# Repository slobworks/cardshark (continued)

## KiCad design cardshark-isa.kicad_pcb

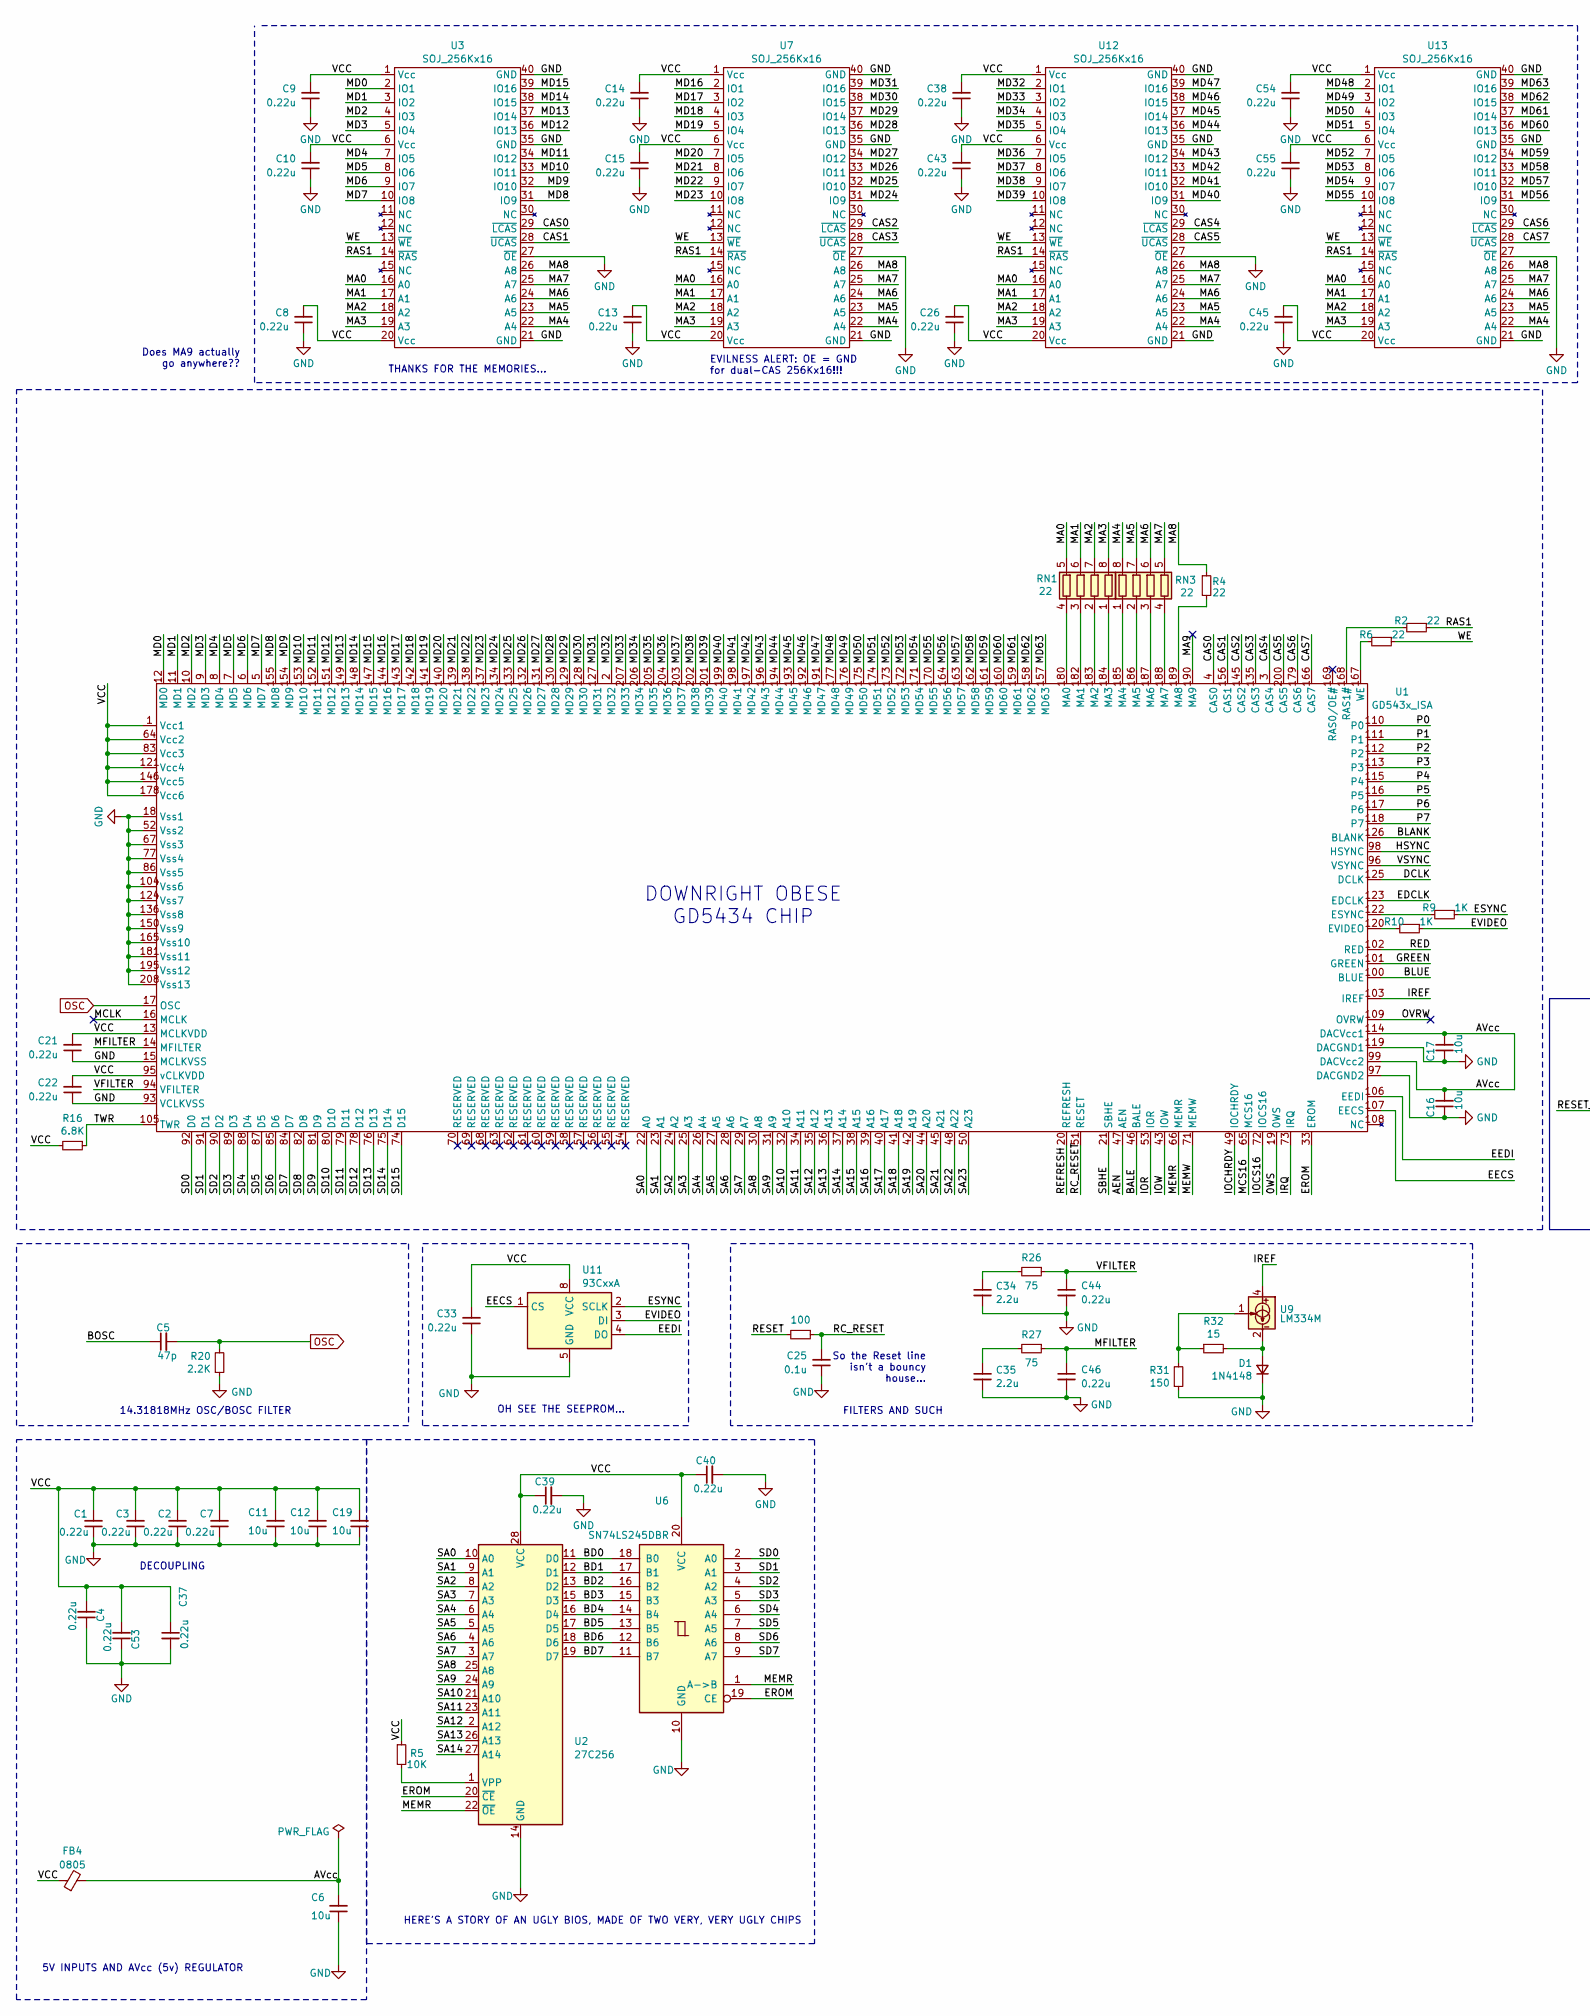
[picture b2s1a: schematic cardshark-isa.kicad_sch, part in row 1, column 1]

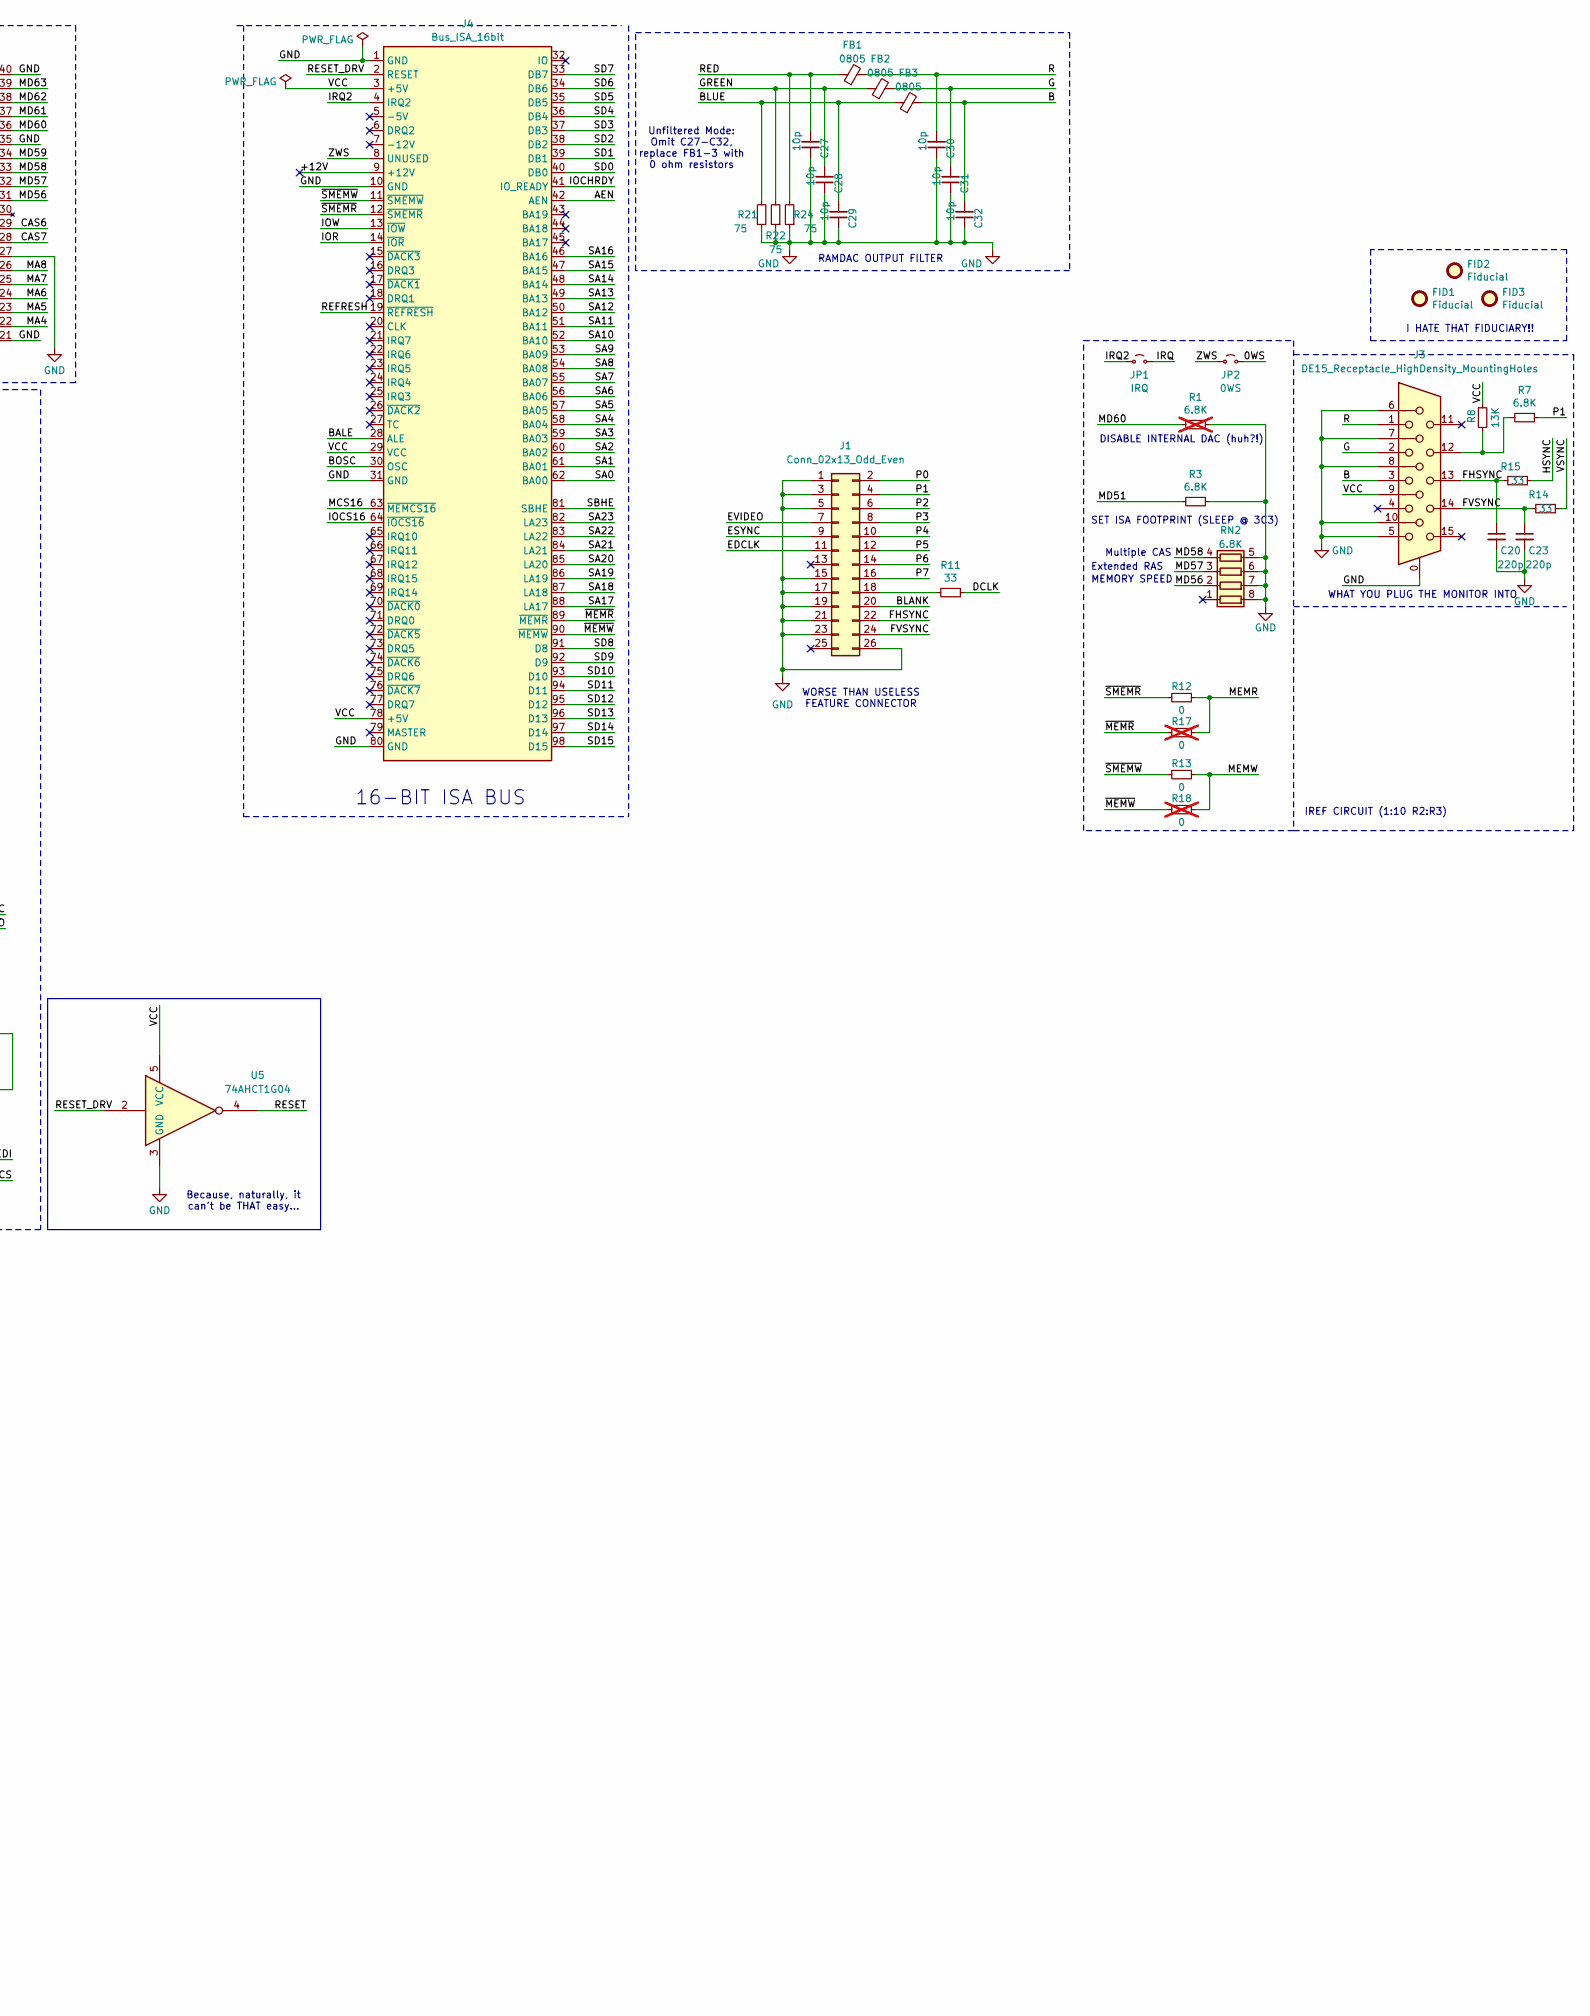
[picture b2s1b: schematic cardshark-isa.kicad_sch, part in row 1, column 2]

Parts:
C1, C2, C3, C4, C7, C8, C9, C10, C13, C14, C15, C21, C22, C26, C33, C37, C38, C39, C40, C43, C44, C45, C46, C53, C54, C55: 0.22u; C_0805_2012Metric
C5: 47p; C_0805_2012Metric
C6, C11, C12, C16, C17, C19: 10u; C_1206_3216Metric
C20, C23: 220p; C_0805_2012Metric
C25: 0.1u; C_0805_2012Metric
C27, C28, C29, C30, C31, C32: 10p; C_0805_2012Metric
C34, C35: 2.2u; C_0805_2012Metric
D1: 1N4148; D_SOD-323_HandSoldering
FB1, FB2, FB3, FB4: 0805; L_0805_2012Metric
FID1, FID2, FID3: Fiducial; Fiducial_1mm_Mask2mm
J1: Conn_02x13_Odd_Even; PinHeader_2x13_P2.54mm_Vertical
J3: DE15_Receptacle_HighDensity_MountingHoles; DSUB-15-HD
J4: Bus_ISA_16bit; BUS_AT
JP1: IRQ; PinHeader_1x02_P2.54mm_Vertical
JP2: 0WS; PinHeader_1x02_P2.54mm_Vertical
R1: 6.8K; R_0805_2012Metric; not fitted
R2, R4, R6: 22; R_0805_2012Metric
R3, R7, R16: 6.8K; R_0805_2012Metric
R5: 10K; R_0805_2012Metric
R8: 13K; R_0805_2012Metric
R9, R10: 1K; R_0805_2012Metric
R11, R14, R15: 33; R_0805_2012Metric
R12, R13: 0; R_0805_2012Metric
R17, R18: 0; R_0805_2012Metric; not fitted
R19: 100; R_0805_2012Metric
R20: 2.2K; R_0805_2012Metric
R21, R22, R24, R26, R27: 75; R_0805_2012Metric
R31: 150; R_0805_2012Metric
R32: 15; R_0805_2012Metric
RN1, RN3: 22; ResArray_Convex_4x0603
RN2: 6.8K; ResArray_Convex_4x0603
U1: GD543x_ISA; PQFP-208_28x28mm_P0.5mm
U2: 27C256; DIP-28_W15.24mm
U3, U7, U12, U13: SOJ_256Kx16; SOJ-40_10.16x26.44mm_P1.27mm
U5: 74AHCT1G04; SOT-353_SC-70-5_Handsoldering
U6: SN74LS245DBR; SSOP-20_5.3x7.2mm_P0.65mm
U9: LM334M; SOIC-8_DMP-8
U11: 93CxxA; SOIC-8_DMP-8

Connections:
/0WS: JP2.2 (B), U1.19 (0WS)
/+12V: J4.9 (+12V)
/AEN: J4.42 (AEN), U1.47 (AEN)
/AVcc: C6.2, C16.2, C17.2, FB4.2, U1.99 (DACVcc2), U1.114 (DACVcc1)
/B: C32.2, FB3.2, J3.3
/BALE: J4.28 (ALE), U1.46 (BALE)
/BD0: U2.11 (D0), U6.18 (B0)
/BD1: U2.12 (D1), U6.17 (B1)
/BD2: U2.13 (D2), U6.16 (B2)
/BD3: U2.15 (D3), U6.15 (B3)
/BD4: U2.16 (D4), U6.14 (B4)
/BD5: U2.17 (D5), U6.13 (B5)
/BD6: U2.18 (D6), U6.12 (B6)
/BD7: U2.19 (D7), U6.11 (B7)
/BLANK: J1.20, U1.126 (BLANK)
/BLUE: C29.2, FB3.1, R21.2, U1.100 (BLUE)
/BOSC: C5.1, J4.30 (OSC)
/CAS0: U1.4 (CAS0), U3.29 (~LCAS)
/CAS1: U1.156 (CAS1), U3.28 (~UCAS)
/CAS2: U1.145 (CAS2), U7.29 (~LCAS)
/CAS3: U1.135 (CAS3), U7.28 (~UCAS)
/CAS4: U1.3 (CAS4), U12.29 (~LCAS)
/CAS5: U1.200 (CAS5), U12.28 (~UCAS)
/CAS6: U1.179 (CAS6), U13.29 (~LCAS)
/CAS7: U1.166 (CAS7), U13.28 (~UCAS)
/DCLK: R11.1, U1.125 (DCLK)
/EDCLK: J1.11, U1.123 (EDCLK)
/EECS: U1.107 (EECS), U11.1 (CS)
/EEDI: U1.106 (EEDI), U11.4 (DO)
/EROM: U1.33 (EROM), U2.20 (~CE), U6.19 (CE)
/ESYNC: J1.9, R9.1, U11.2 (SCLK)
/EVIDEO: J1.7, R10.1, U11.3 (DI)
/FHSYNC: C20.1, J1.22, J3.13, R15.2
/FVSYNC: C23.1, J1.24, J3.14, R14.2
/G: C31.2, FB2.2, J3.2
/GREEN: C28.2, FB2.1, R22.2, U1.101 (GREEN)
/HSYNC: R15.1, U1.98 (HSYNC)
/IOCHRDY: J4.41 (IO_READY), U1.49 (IOCHRDY)
/IOCS16: J4.64 (~IOCS16), U1.72 (IOCS16)
/IOR: J4.14 (~IOR), U1.53 (IOR)
/IOW: J4.13 (~IOW), U1.43 (IOW)
/IREF: U1.103 (IREF), U9.4
/IRQ: JP1.2 (B), U1.73 (IRQ)
/IRQ2: J4.4 (IRQ2), JP1.1 (A)
/MA0: RN1.5 (R4.2), U3.16 (A0), U7.16 (A0), U12.16 (A0), U13.16 (A0)
/MA1: RN1.6 (R3.2), U3.17 (A1), U7.17 (A1), U12.17 (A1), U13.17 (A1)
/MA2: RN1.7 (R2.2), U3.18 (A2), U7.18 (A2), U12.18 (A2), U13.18 (A2)
/MA3: RN1.8 (R1.2), U3.19 (A3), U7.19 (A3), U12.19 (A3), U13.19 (A3)
/MA4: RN3.8 (R1.2), U3.22 (A4), U7.22 (A4), U12.22 (A4), U13.22 (A4)
/MA5: RN3.7 (R2.2), U3.23 (A5), U7.23 (A5), U12.23 (A5), U13.23 (A5)
/MA6: RN3.6 (R3.2), U3.24 (A6), U7.24 (A6), U12.24 (A6), U13.24 (A6)
/MA7: RN3.5 (R4.2), U3.25 (A7), U7.25 (A7), U12.25 (A7), U13.25 (A7)
/MA8: R4.1, U3.26 (A8), U7.26 (A8), U12.26 (A8), U13.26 (A8)
/MA9: U1.190 (MA9)
/MCLK: U1.16 (MCLK)
/MCS16: J4.63 (~MEMCS16), U1.65 (MCS16)
/MD0: U1.12 (MD0), U3.2 (IO1)
/MD1: U1.11 (MD1), U3.3 (IO2)
/MD2: U1.10 (MD2), U3.4 (IO3)
/MD3: U1.9 (MD3), U3.5 (IO4)
/MD4: U1.8 (MD4), U3.7 (IO5)
/MD5: U1.7 (MD5), U3.8 (IO6)
/MD6: U1.6 (MD6), U3.9 (IO7)
/MD7: U1.5 (MD7), U3.10 (IO8)
/MD8: U1.155 (MD8), U3.31 (IO9)
/MD9: U1.154 (MD9), U3.32 (IO10)
/MD10: U1.153 (MD10), U3.33 (IO11)
/MD11: U1.152 (MD11), U3.34 (IO12)
/MD12: U1.151 (MD12), U3.36 (IO13)
/MD13: U1.149 (MD13), U3.37 (IO14)
/MD14: U1.148 (MD14), U3.38 (IO15)
/MD15: U1.147 (MD15), U3.39 (IO16)
/MD16: U1.144 (MD16), U7.2 (IO1)
/MD17: U1.143 (MD17), U7.3 (IO2)
/MD18: U1.142 (MD18), U7.4 (IO3)
/MD19: U1.141 (MD19), U7.5 (IO4)
/MD20: U1.140 (MD20), U7.7 (IO5)
/MD21: U1.139 (MD21), U7.8 (IO6)
/MD22: U1.138 (MD22), U7.9 (IO7)
/MD23: U1.137 (MD23), U7.10 (IO8)
/MD24: U1.134 (MD24), U7.31 (IO9)
/MD25: U1.133 (MD25), U7.32 (IO10)
/MD26: U1.132 (MD26), U7.33 (IO11)
/MD27: U1.131 (MD27), U7.34 (IO12)
/MD28: U1.130 (MD28), U7.36 (IO13)
/MD29: U1.129 (MD29), U7.37 (IO14)
/MD30: U1.128 (MD30), U7.38 (IO15)
/MD31: U1.127 (MD31), U7.39 (IO16)
/MD32: U1.2 (MD32), U12.2 (IO1)
/MD33: U1.207 (MD33), U12.3 (IO2)
/MD34: U1.206 (MD34), U12.4 (IO3)
/MD35: U1.205 (MD35), U12.5 (IO4)
/MD36: U1.204 (MD36), U12.7 (IO5)
/MD37: U1.203 (MD37), U12.8 (IO6)
/MD38: U1.202 (MD38), U12.9 (IO7)
/MD39: U1.201 (MD39), U12.10 (IO8)
/MD40: U1.199 (MD40), U12.31 (IO9)
/MD41: U1.198 (MD41), U12.32 (IO10)
/MD42: U1.197 (MD42), U12.33 (IO11)
/MD43: U1.196 (MD43), U12.34 (IO12)
/MD44: U1.194 (MD44), U12.36 (IO13)
/MD45: U1.193 (MD45), U12.37 (IO14)
/MD46: U1.192 (MD46), U12.38 (IO15)
/MD47: U1.191 (MD47), U12.39 (IO16)
/MD48: U1.177 (MD48), U13.2 (IO1)
/MD49: U1.176 (MD49), U13.3 (IO2)
/MD50: U1.175 (MD50), U13.4 (IO3)
/MD51: R3.2, U1.174 (MD51), U13.5 (IO4)
/MD52: U1.173 (MD52), U13.7 (IO5)
/MD53: U1.172 (MD53), U13.8 (IO6)
/MD54: U1.171 (MD54), U13.9 (IO7)
/MD55: U1.170 (MD55), U13.10 (IO8)
/MD56: RN2.2 (R2.1), U1.164 (MD56), U13.31 (IO9)
/MD57: RN2.3 (R3.1), U1.163 (MD57), U13.32 (IO10)
/MD58: RN2.4 (R4.1), U1.162 (MD58), U13.33 (IO11)
/MD59: U1.161 (MD59), U13.34 (IO12)
/MD60: R1.2, U1.160 (MD60), U13.36 (IO13)
/MD61: U1.159 (MD61), U13.37 (IO14)
/MD62: U1.158 (MD62), U13.38 (IO15)
/MD63: U1.157 (MD63), U13.39 (IO16)
/MEMR: R12.1, R17.1, U1.66 (MEMR), U2.22 (~OE), U6.1 (A->B)
/MEMW: R13.1, R18.1, U1.71 (MEMW)
/MFILTER: C46.1, R27.1, U1.14 (MFILTER)
/OVRW: U1.109 (OVRW)
/P0: J1.2, U1.110 (P0)
/P1: J1.4, R7.1, U1.111 (P1)
/P2: J1.6, U1.112 (P2)
/P3: J1.8, U1.113 (P3)
/P4: J1.10, U1.115 (P4)
/P5: J1.12, U1.116 (P5)
/P6: J1.14, U1.117 (P6)
/P7: J1.16, U1.118 (P7)
/R: C30.2, FB1.2, J3.1
/RAS1: R2.1, U3.14 (~RAS), U7.14 (~RAS), U12.14 (~RAS), U13.14 (~RAS)
/RC_RESET: C25.2, R19.1, U1.51 (RESET)
/RED: C27.2, FB1.1, R24.2, U1.102 (RED)
/REFRESH: J4.19 (~REFRESH), U1.20 (REFRESH)
/RESET: R19.2, U5.4
/RESET_DRV: J4.2 (RESET), U5.2
/SA0: J4.62 (BA00), U1.22 (A0), U2.10 (A0)
/SA1: J4.61 (BA01), U1.23 (A1), U2.9 (A1)
/SA2: J4.60 (BA02), U1.24 (A2), U2.8 (A2)
/SA3: J4.59 (BA03), U1.25 (A3), U2.7 (A3)
/SA4: J4.58 (BA04), U1.26 (A4), U2.6 (A4)
/SA5: J4.57 (BA05), U1.27 (A5), U2.5 (A5)
/SA6: J4.56 (BA06), U1.28 (A6), U2.4 (A6)
/SA7: J4.55 (BA07), U1.29 (A7), U2.3 (A7)
/SA8: J4.54 (BA08), U1.30 (A8), U2.25 (A8)
/SA9: J4.53 (BA09), U1.31 (A9), U2.24 (A9)
/SA10: J4.52 (BA10), U1.32 (A10), U2.21 (A10)
/SA11: J4.51 (BA11), U1.34 (A11), U2.23 (A11)
/SA12: J4.50 (BA12), U1.35 (A12), U2.2 (A12)
/SA13: J4.49 (BA13), U1.36 (A13), U2.26 (A13)
/SA14: J4.48 (BA14), U1.37 (A14), U2.27 (A14)
/SA15: J4.47 (BA15), U1.38 (A15)
/SA16: J4.46 (BA16), U1.39 (A16)
/SA17: J4.88 (LA17), U1.40 (A17)
/SA18: J4.87 (LA18), U1.41 (A18)
/SA19: J4.86 (LA19), U1.42 (A19)
/SA20: J4.85 (LA20), U1.44 (A20)
/SA21: J4.84 (LA21), U1.45 (A21)
/SA22: J4.83 (LA22), U1.48 (A22)
/SA23: J4.82 (LA23), U1.50 (A23)
/SBHE: J4.81 (SBHE), U1.21 (SBHE)
/SD0: J4.40 (DB0), U1.92 (D0), U6.2 (A0)
/SD1: J4.39 (DB1), U1.91 (D1), U6.3 (A1)
/SD2: J4.38 (DB2), U1.90 (D2), U6.4 (A2)
/SD3: J4.37 (DB3), U1.89 (D3), U6.5 (A3)
/SD4: J4.36 (DB4), U1.88 (D4), U6.6 (A4)
/SD5: J4.35 (DB5), U1.87 (D5), U6.7 (A5)
/SD6: J4.34 (DB6), U1.85 (D6), U6.8 (A6)
/SD7: J4.33 (DB7), U1.84 (D7), U6.9 (A7)
/SD8: J4.91 (D8), U1.82 (D8)
/SD9: J4.92 (D9), U1.81 (D9)
/SD10: J4.93 (D10), U1.80 (D10)
/SD11: J4.94 (D11), U1.79 (D11)
/SD12: J4.95 (D12), U1.78 (D12)
/SD13: J4.96 (D13), U1.76 (D13)
/SD14: J4.97 (D14), U1.75 (D14)
/SD15: J4.98 (D15), U1.74 (D15)
/TWR: R16.1, U1.105 (TWR)
/VCC: C1.2, C2.2, C3.2, C4.2, C7.2, C8.2, C9.2, C10.2, C11.2, C12.2, C13.2, C14.2, C15.2, C19.2, C21.2, C22.2, C26.2, C33.2, C37.1, C38.2, C39.1, C40.1, C43.2, C45.2, C53.2, C54.2, C55.2, FB4.1, J3.9, J4.3 (+5V), J4.29 (VCC), J4.78 (+5V), R5.1, R8.1, R16.2, U1.1 (Vcc1), U1.13 (MCLKVDD), U1.64 (Vcc2), U1.83 (Vcc3), U1.95 (vCLKVDD), U1.121 (Vcc4), U1.146 (Vcc5), U1.178 (Vcc6), U2.28 (VCC), U3.1 (Vcc), U3.6 (Vcc), U3.20 (Vcc), U5.5 (VCC), U6.20 (VCC), U7.1 (Vcc), U7.6 (Vcc), U7.20 (Vcc), U11.8 (VCC), U12.1 (Vcc), U12.6 (Vcc), U12.20 (Vcc), U13.1 (Vcc), U13.6 (Vcc), U13.20 (Vcc)
/VFILTER: C44.1, R26.1, U1.94 (VFILTER)
/VSYNC: R14.1, U1.96 (VSYNC)
/WE: R6.1, U3.13 (~WE), U7.13 (~WE), U12.13 (~WE), U13.13 (~WE)
/ZWS: J4.8 (UNUSED), JP2.1 (A)
/~MEMR: J4.89 (~MEMR), R17.2
/~MEMW: J4.90 (~MEMW), R18.2
/~SMEMR: J4.12 (~SMEMR), R12.2
/~SMEMW: J4.11 (~SMEMW), R13.2
GND: C1.1, C2.1, C3.1, C4.1, C6.1, C7.1, C8.1, C9.1, C10.1, C11.1, C12.1, C13.1, C14.1, C15.1, C16.1, C17.1, C19.1, C20.2, C21.1, C22.1, C23.2, C25.1, C26.1, C27.1, C28.1, C29.1, C30.1, C31.1, C32.1, C33.1, C34.2, C35.2, C37.2, C38.1, C39.2, C40.2, C43.1, C44.2, C45.1, C46.2, C53.1, C54.1, C55.1, D1.1 (K), J1.1, J1.3, J1.5, J1.15, J1.17, J1.19, J1.21, J1.23, J1.26, J3.0, J3.5, J3.6, J3.7, J3.8, J3.10, J4.1 (GND), J4.10 (GND), J4.31 (GND), J4.80 (GND), R1.1, R3.1, R20.1, R21.1, R22.1, R24.1, R31.1, RN2.5 (R4.2), RN2.6 (R3.2), RN2.7 (R2.2), RN2.8 (R1.2), U1.15 (MCLKVSS), U1.18 (Vss1), U1.52 (Vss2), U1.67 (Vss3), U1.77 (Vss4), U1.86 (Vss5), U1.93 (VCLKVSS), U1.97 (DACGND2), U1.104 (Vss6), U1.119 (DACGND1), U1.124 (Vss7), U1.136 (Vss8), U1.150 (Vss9), U1.165 (Vss10), U1.181 (Vss11), U1.195 (Vss12), U1.208 (Vss13), U2.14 (GND), U3.21 (GND), U3.27 (~OE), U3.35 (GND), U3.40 (GND), U5.3 (GND), U6.10 (GND), U7.21 (GND), U7.27 (~OE), U7.35 (GND), U7.40 (GND), U11.5 (GND), U12.21 (GND), U12.27 (~OE), U12.35 (GND), U12.40 (GND), U13.21 (GND), U13.27 (~OE), U13.35 (GND), U13.40 (GND)
unnamed: C34.1, R26.2
unnamed: C35.1, R27.2
unnamed: D1.2 (A), R32.2, U9.2, U9.3, U9.6, U9.7
unnamed: J1.18, R11.2
unnamed: J3.12, R7.2, R8.2
unnamed: R31.2, R32.1, U9.1
unnamed: RN1.1 (R1.1), U1.184 (MA3)
unnamed: RN1.2 (R2.1), U1.183 (MA2)
unnamed: RN1.3 (R3.1), U1.182 (MA1)
unnamed: RN1.4 (R4.1), U1.180 (MA0)
unnamed: RN3.1 (R1.1), U1.185 (MA4)
unnamed: RN3.2 (R2.1), U1.186 (MA5)
unnamed: RN3.3 (R3.1), U1.187 (MA6)
unnamed: RN3.4 (R4.1), U1.188 (MA7)
unnamed: R9.2, U1.122 (ESYNC)
unnamed: R10.2, U1.120 (EVIDEO)
unnamed: R4.2, U1.189 (MA8)
unnamed: R2.2, U1.168 (RAS1#)
unnamed: R6.2, U1.167 (WE)
unnamed: R5.2, U2.1 (VPP)
OSC: C5.2, R20.2, U1.17 (OSC)

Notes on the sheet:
Unfiltered Mode: Omit C27-C32, replace FB1-3 with 0 ohm resistors
Because, naturally, it can't be THAT easy...
16-BIT ISA BUS
HERE'S A STORY OF AN UGLY BIOS, MADE OF TWO VERY, VERY UGLY CHIPS
Multiple CAS
DOWNRIGHT OBESE GD5434 CHIP
So the Reset line isn't a bouncy house...
FILTERS AND SUCH
WORSE THAN USELESS FEATURE CONNECTOR
IREF CIRCUIT (1:10 R2:R3)
14.31818MHz OSC/BOSC FILTER
Does MA9 actually go anywhere??
THANKS FOR THE MEMORIES...
MEMORY SPEED
5V INPUTS AND AVcc (5v) REGULATOR
SET ISA FOOTPRINT (SLEEP @ 3C3)
WHAT YOU PLUG THE MONITOR INTO
OH SEE THE SEEPROM...
DISABLE INTERNAL DAC (huh?!)
RAMDAC OUTPUT FILTER
I HATE THAT FIDUCIARY!!
Extended RAS
DECOUPLING
EVILNESS ALERT: OE = GND for dual-CAS 256Kx16!!!

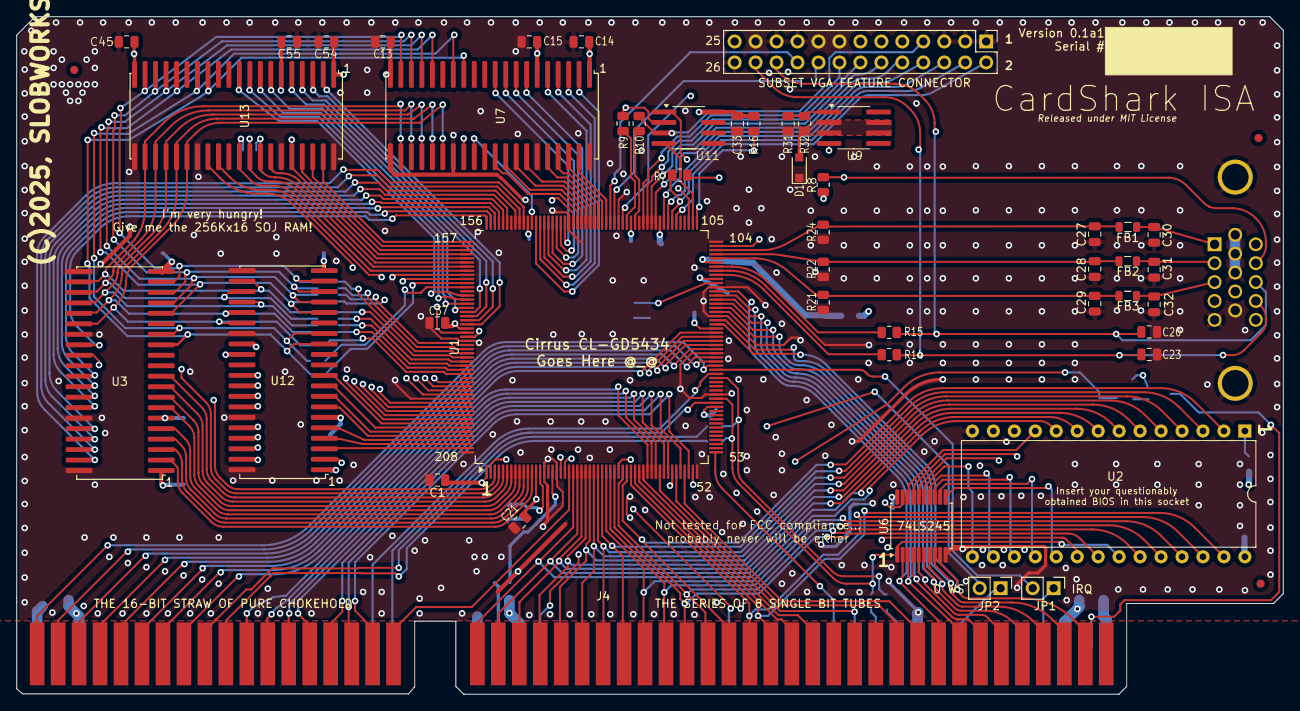
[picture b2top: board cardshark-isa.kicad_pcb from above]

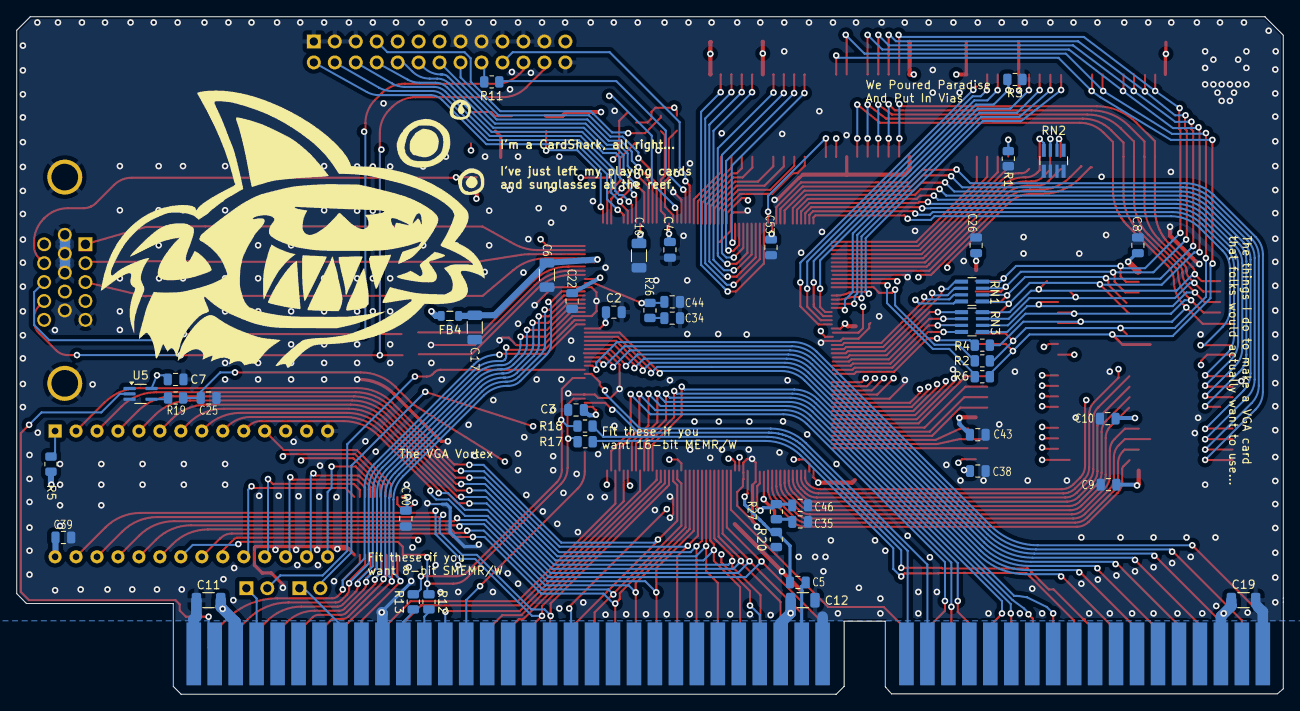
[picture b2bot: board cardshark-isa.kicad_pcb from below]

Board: 4 copper layers, 153.5 x 82.1 mm, 97 parts (46 on the bottom side), 208 nets.

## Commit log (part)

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2025-01-08 Create LICENSE
2025-01-08 Add files via upload
    Naturally I'd forget the CSV BOM... there you go.
2025-01-08 Add files via upload
    A bunch of quick changes
2025-01-09 Add files via upload
    Cleaned up PCB graphics to make them actually vaguely fabbable
2025-01-10 Add files via upload
    Hasty bug-fix to a nasty broken PLCC-32 socket problem
2025-01-19 Delete new_parts directory
    Broken! Broken! Broken! Broken?
2025-01-19 Add files via upload
    Big bunch'o little minor fixes, no version number change (mostly to clean up libraries and eliminate a bunch of previously silenced ERC warnings)
2025-09-04 Add files via upload
    Uploaded ISA version files
2025-09-04 Delete cardshark-cache.lib
    Removing buggy VLB version files
2025-09-04 Delete cardshark-backups directory
    Removing buggy VLB version files
2025-09-04 Delete cardshark-B_Cu.gbr
    Removing buggy VLB version files
2025-09-04 Delete cardshark-B_Mask.gbr
    Removing buggy VLB version files
2025-09-04 Delete cardshark-B_Paste.gbr
    Removing buggy VLB version files
2025-09-04 Delete cardshark-B_Silkscreen.gbr
    Removing buggy VLB version files
2025-09-04 Delete cardshark-Edge_Cuts.gbr
    Removing buggy VLB version files
2025-09-04 Delete cardshark-F_Cu.gbr
    Removing buggy VLB version files
2025-09-04 Delete cardshark-F_Mask.gbr
    Removing buggy VLB version files
2025-09-04 Delete cardshark-F_Paste.gbr
    Removing buggy VLB version files
2025-09-04 Delete cardshark-GND_Cu.gbr
    Removing buggy VLB version files
2025-09-04 Delete cardshark.bom
    Removing buggy VLB version files
2025-09-04 Delete cardshark-job.gbrjob
    Removing buggy VLB version files
2025-09-04 Delete cardshark-rescue.dcm
    Removing buggy VLB version files
2025-09-04 Delete cardshark-rescue.kicad_sym
    Removing buggy VLB version files
2025-09-04 Delete cardshark-rescue.lib
    Removing buggy VLB version files
2025-09-04 Delete cardshark.kicad_pcb
    Removing buggy VLB version files
2025-09-04 Delete cardshark.kicad_prl
    Removing buggy VLB version files
2025-09-04 Delete cardshark.kicad_pro
    Removing buggy VLB version files
2025-09-04 Delete cardshark.kicad_sch
    Removing buggy VLB version files
2025-09-04 Delete cardshark.xml
    Removing buggy VLB version files
2025-09-04 Delete carshark.kicad_prl
    Removing buggy VLB version files
2025-09-04 Delete cardshark-NPTH-drl_map.gbr
    Removing buggy VLB version files
2025-09-04 Delete cardshark-NPTH.drl
    Removing buggy VLB version files
2025-09-04 Delete cardshark-PTH-drl_map.gbr
    Removing buggy VLB version files
2025-09-04 Delete cardshark-PTH.drl
    Removing buggy VLB version files
2025-09-04 Delete cardshark-Vcc_Cu.gbr
    Removing buggy VLB version files
2025-09-04 Update README.md
    New pictures
2025-09-04 Add files via upload
    Uploaded wrong version of board files by mistake; uploaded correct working version this time
2025-09-04 Delete cardshark-backups directory
    Deleting crappy broken VLB version files
2025-09-04 Delete new_parts directory
    Deleting crappy broken VLB version files
2025-09-04 Delete cardshark-B_Cu.gbr
    Deleting crappy broken VLB version files
2025-09-04 Delete cardshark-B_Mask.gbr
    Deleting crappy broken VLB version files
2025-09-04 Delete cardshark-B_Paste.gbr
    Deleting crappy broken VLB version files
2025-09-04 Delete cardshark-B_Silkscreen.gbr
    Deleting crappy broken VLB version files
2025-09-04 Delete cardshark-Edge_Cuts.gbr
    Deleting crappy broken VLB version files
2025-09-04 Delete cardshark-F_Cu.gbr
    Deleting crappy broken VLB version files
2025-09-04 Delete cardshark-F_Mask.gbr
    Deleting crappy broken VLB version files
2025-09-04 Delete cardshark-F_Paste.gbr
    Deleting crappy broken VLB version files
2025-09-04 Delete cardshark-F_Silkscreen.gbr
    Deleting crappy broken VLB version files
2025-09-04 Delete cardshark-GND_Cu.gbr
    Deleting crappy broken VLB version files
2025-09-04 Delete cardshark-NPTH-drl_map.gbr
    Deleting crappy broken VLB version files
2025-09-04 Delete cardshark-NPTH.drl
    Deleting crappy broken VLB version files
2025-09-04 Delete cardshark-PTH-drl_map.gbr
    Deleting crappy broken VLB version files
2025-09-04 Delete cardshark-PTH.drl
    Deleting crappy broken VLB version files
2025-09-04 Delete cardshark-Vcc_Cu.gbr
    Deleting crappy broken VLB version files
2025-09-04 Delete cardshark-cache.lib
    Deleting crappy broken VLB version files
2025-09-04 Delete cardshark-rescue.dcm
    Deleting crappy broken VLB version files
2025-09-04 Delete cardshark-job.gbrjob
    Deleting crappy broken VLB version files
2025-09-04 Delete cardshark-rescue.kicad_sym
    Deleting crappy broken VLB version files
2025-09-04 Delete cardshark-rescue.lib
    Deleting crappy broken VLB version files
2025-09-04 Delete cardshark.bom
    Deleting crappy broken VLB version files
2025-09-04 Delete cardshark.kicad_pcb
    Deleting crappy broken VLB version files
2025-09-04 Delete cardshark.kicad_prl
    Deleting crappy broken VLB version files
2025-09-04 Delete cardshark.kicad_pro
    Deleting crappy broken VLB version files
2025-09-04 Delete cardshark.kicad_sch
    Deleting crappy broken VLB version files
2025-09-04 Delete cardshark.xml
    Deleting crappy broken VLB version files
2025-09-04 Delete carshark.kicad_prl
    Deleting crappy broken VLB version files
2025-09-04 Delete fp-info-cache
    Deleting crappy broken VLB version files
2025-09-04 Delete fp-lib-table
    Deleting crappy broken VLB version files
2025-09-04 Delete sym-lib-table
    Deleting crappy broken VLB version files
2025-09-04 Delete ~cardshark.kicad_pcb.lck
    Deleting crappy broken VLB version files
2025-09-04 Delete ~cardshark.kicad_sch.lck
    Deleting crappy broken VLB version files
2025-09-04 Add files via upload
    Uploaded CSV BOM. Made various little, very minor quick fixes, mostly of a cosmetic nature.
